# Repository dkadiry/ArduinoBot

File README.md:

# ArduinoBot
This repo contains source codes for a Line follwer Robot with Obstacle Avoidance Capabilities and bluetooth power control

# File Descriptions
* [testingfinal23](https://github.com/dkadiry/ArduinoBot/blob/main/testingfinal23.ino) - Arduino control file
* [OKADIRI_1stGroup.brd](https://github.com/dkadiry/ArduinoBot/blob/main/OKADIRI_1stGroup.brd) - Eagle PCB file
* [OKADIRI_1stGroup.brd](https://github.com/dkadiry/ArduinoBot/blob/main/OKADIRI_1stGroup.sch) - Circuit Schematic file

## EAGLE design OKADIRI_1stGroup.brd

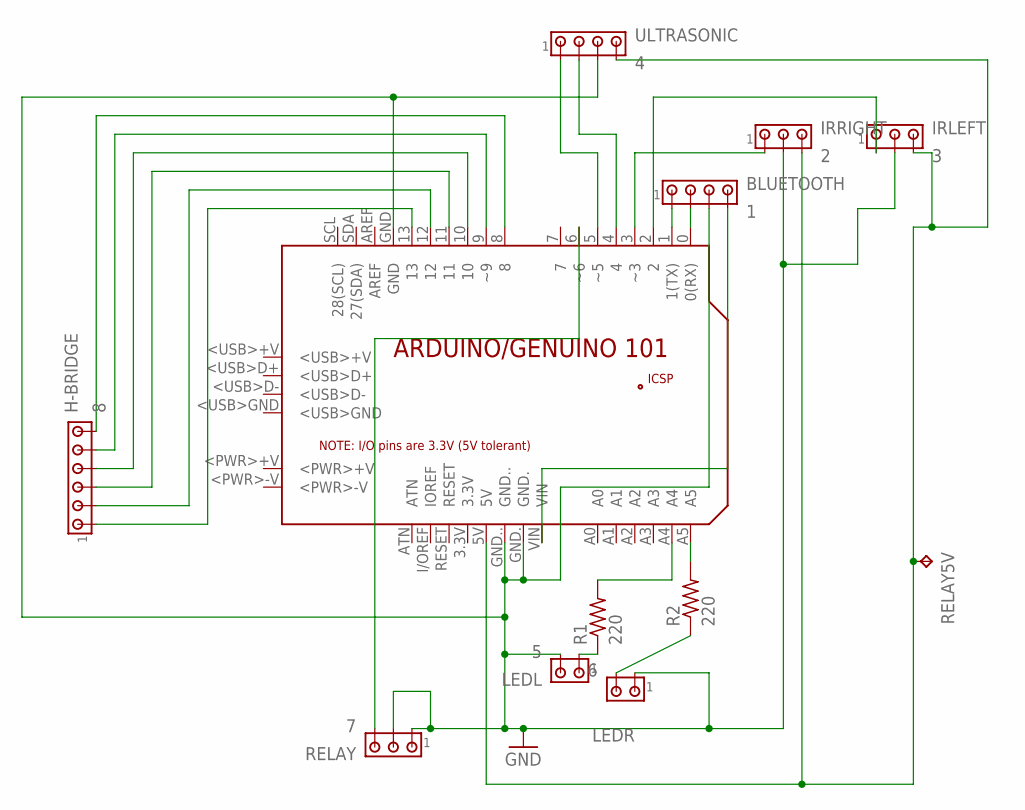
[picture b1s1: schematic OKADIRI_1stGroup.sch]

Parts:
BLUETOOTH: 1; 10X04MTA
H-BRIDGE: 8; 10X06MTA
IRLEFT: 3; 10X03MTA
IRRIGHT: 2; 10X03MTA
LEDL: 5; 10X02MTA
LEDR: 6; 10X02MTA
PCB1: ARDUINO_101
R1, R2: 220; 0309/10
RELAY: 7; 10X03MTA
RELAY5V: TPPAD1-13Y; P1-13Y
ULTRASONIC: 4; 10X04MTA

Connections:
GND: BLUETOOTH.3, IRLEFT.2, IRRIGHT.2, LEDL.2, LEDR.1, PCB1.GND, PCB1.GND., PCB1.GND.., RELAY.1, RELAY.2, ULTRASONIC.3
unnamed: BLUETOOTH.1, PCB1.1 (1(TX))
unnamed: IRLEFT.1, PCB1.2
unnamed: BLUETOOTH.2, PCB1.0 (0(RX))
unnamed: BLUETOOTH.4, PCB1.VIN
unnamed: LEDL.1, R1.1
unnamed: PCB1.A4, R1.2
unnamed: IRRIGHT.1, PCB1.3 (~3)
unnamed: PCB1.A5, R2.2
unnamed: PCB1.4, ULTRASONIC.2
unnamed: LEDR.2, R2.1
unnamed: PCB1.5 (~5), ULTRASONIC.1
unnamed: PCB1.6 (~6), RELAY.3
unnamed: H-BRIDGE.6, PCB1.8
unnamed: H-BRIDGE.5, PCB1.9 (~9)
unnamed: H-BRIDGE.4, PCB1.10
unnamed: H-BRIDGE.3, PCB1.11
unnamed: H-BRIDGE.2, PCB1.12
unnamed: H-BRIDGE.1, PCB1.13
unnamed: IRLEFT.3, IRRIGHT.3, PCB1.5V, RELAY5V.TP, ULTRASONIC.4

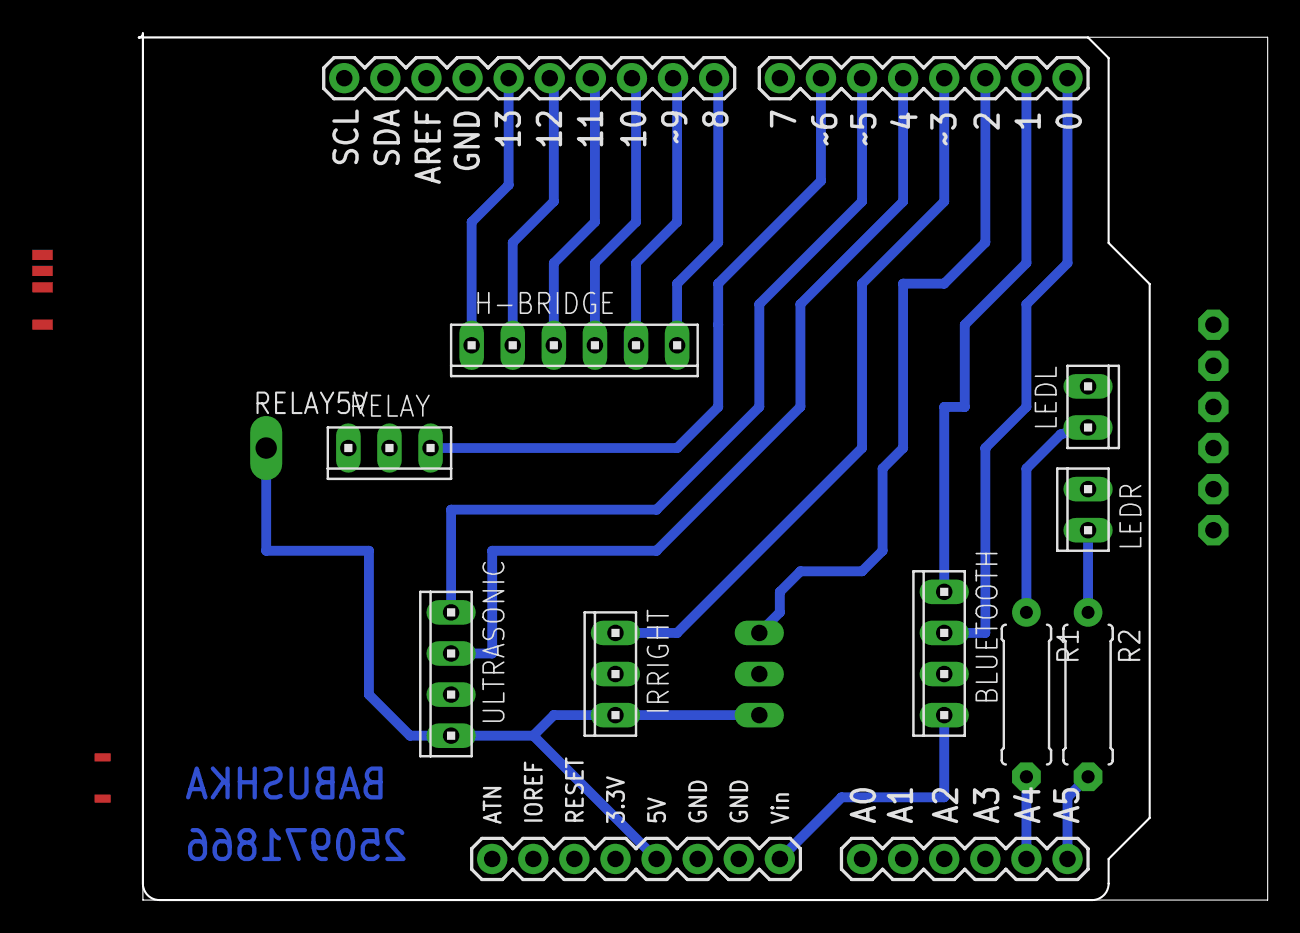
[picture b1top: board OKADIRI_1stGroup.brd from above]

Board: 2 copper layers, 69.5 x 53.3 mm, 12 parts (1 on the bottom side), 20 nets.

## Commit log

2023-04-13 Adding Arduino Control Logic
2023-04-13 Adding Circuit Schematic
